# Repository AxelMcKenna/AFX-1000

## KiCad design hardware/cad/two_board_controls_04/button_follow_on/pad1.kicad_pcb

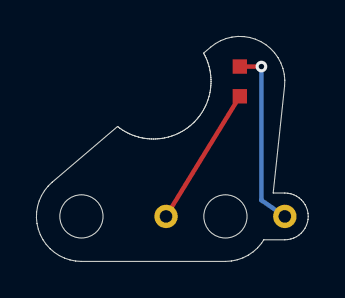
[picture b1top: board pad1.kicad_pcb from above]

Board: 2 copper layers, 15.1 x 12.5 mm, 5 parts (0 on the bottom side), 2 nets.

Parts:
D1: KPT-1608CGCK; KPT1608
H1, H2: Existing holder mount; M2
W1: LED_K; Wire
W2: LED_A; Wire

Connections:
LED_A: D1.2, W2.1
LED_K: D1.1, W1.1

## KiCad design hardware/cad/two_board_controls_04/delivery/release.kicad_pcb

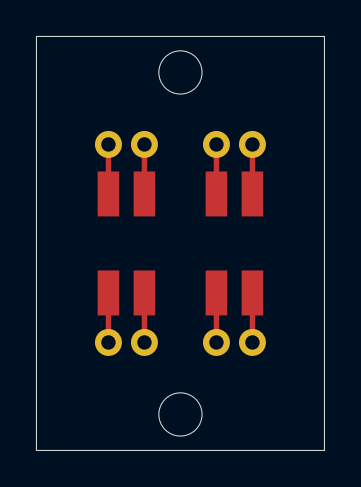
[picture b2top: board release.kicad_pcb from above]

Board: 2 copper layers, 16.0 x 23.0 mm, 11 parts (0 on the bottom side), 8 nets.

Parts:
H1, H2: M2
SW1: JS203011SCQN
W1: SW_PIN_1; WirePad
W2: SW_PIN_2; WirePad
W3: SW_PIN_3; WirePad
W4: SW_PIN_4; WirePad
W5: SW_PIN_5; WirePad
W6: SW_PIN_6; WirePad
W7: SW_PIN_7; WirePad
W8: SW_PIN_8; WirePad

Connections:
SW_PIN_1: SW1.1, W1.1
SW_PIN_2: SW1.2, W2.1
SW_PIN_3: SW1.3, W3.1
SW_PIN_4: SW1.4, W4.1
SW_PIN_5: SW1.5, W5.1
SW_PIN_6: SW1.6, W6.1
SW_PIN_7: SW1.7, W7.1
SW_PIN_8: SW1.8, W8.1

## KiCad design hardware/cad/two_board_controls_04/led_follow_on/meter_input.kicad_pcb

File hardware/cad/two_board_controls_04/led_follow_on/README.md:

# Meter and bank emitter checkpoint

This follow-on implements two 20-emitter meter boards and four copies of one bank-emitter board. The 44 sink channels are bound to the existing integrated signal PCB by `wiring.csv` and its source-hashed review. All emitters are Kingbright KPT-1608CGCK with manufacturer-derived lands, polarity, body tolerances and optical locations. This green population establishes physical fit; final meter color progression and brightness remain optical acceptance work.

Each board is retained with M2 screws, washers and nuts. The printed opaque frame separates meter cells and holds the retained lens flange against the lid. Meter boards occupyZ39.3–40.9; bank boardsZ39.6–41.2. Meter mounts are(43.9,14.75),(100.9,14.75),(43.9,41.75),(100.9,41.75). Bank mounts areX76/95/114/133, each atY97 and 102. Use M2×10 screws with head OD≤4.5, M2 nuts AF4×1.6 and 0.5 mm washers. Meter nuts beginZ37.2, bank nutsZ37.5. Confirm actual hardware and printed stack before assembly.

`meters-r4` passes seven empty clearances (including full button travel and all 42 local wire exits), two retention probes and two printable frames. `banks-r4` passes seven empty clearances, two retention probes and seven printable exports including combined full/split lid and guide. The combined exports include sealed TBH04 display/selector modifications. Existing lenses are retained. `pcb-native-r3/review.json` records zero native DRC violations and zero unconnected items for all three distinct routed board designs. This is board connectivity verification, not schematic ERC or powered qualification.

`banks-r3/led_guide` is retained failed evidence: CGAL emitted two degenerate collinear facets and four bad directed edges. Re-exporting with the pinned Manifold backend passed the same closed-oriented-boundary check in r4; no geometry was weakened to bypass the check. Earlier bank r1 caught incomplete imported button-parameter scope; `button_motion.scad` now imports through the complete housing parameter scope.

For integration use `tbh 05_bank_meter_installed()`, `tbh 05_bank_meter_lid()` and `tbh 05_bank_meter_guide()` from `banks.scad`. The installed module includes purchased-body and local lead reserves for collision review. Frame exports are print-oriented; installed modules use housing datums.

Anode leads need rated harness splices, not several conductors in one crimp. Local wire envelopes reserve only the first 2.5 mm below each board. Full harness routing, strain relief, solder insulation and lid-service loops remain separate gates. Tiny boards and .4 mm cell walls require fabrication/print capability confirmation. There is no physical or optical acceptance claim. Button-indicator and RGB-ring carriers are not implemented by this checkpoint and must not be inferred from the 44 implemented channels.

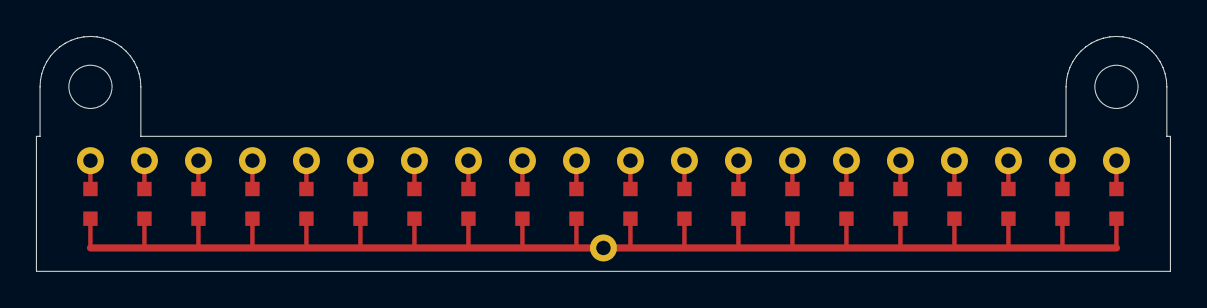
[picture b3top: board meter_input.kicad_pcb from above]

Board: 2 copper layers, 63.0 x 13.1 mm, 43 parts (0 on the bottom side), 21 nets.

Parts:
D1, D2, D3, D4, D5, D6, D7, D8, D9, D10, D11, D12, D13, D14, D15, D16, D17, D18, D19, D20: KPT-1608CGCK; KPT1608
H1, H2: M2
W1: meter_input_0; WirePad
W2: meter_input_1; WirePad
W3: meter_input_2; WirePad
W4: meter_input_3; WirePad
W5: meter_input_4; WirePad
W6: meter_input_5; WirePad
W7: meter_input_6; WirePad
W8: meter_input_7; WirePad
W9: meter_input_8; WirePad
W10: meter_input_9; WirePad
W11: meter_input_10; WirePad
W12: meter_input_11; WirePad
W13: meter_input_12; WirePad
W14: meter_input_13; WirePad
W15: meter_input_14; WirePad
W16: meter_input_15; WirePad
W17: meter_input_16; WirePad
W18: meter_input_17; WirePad
W19: meter_input_18; WirePad
W20: meter_input_19; WirePad
WA: LED_ANODE_5V; WirePad

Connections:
LED_ANODE_5V: D1.2, D2.2, D3.2, D4.2, D5.2, D6.2, D7.2, D8.2, D9.2, D10.2, D11.2, D12.2, D13.2, D14.2, D15.2, D16.2, D17.2, D18.2, D19.2, D20.2, WA.1
meter_input_0: D1.1, W1.1
meter_input_1: D2.1, W2.1
meter_input_2: D3.1, W3.1
meter_input_3: D4.1, W4.1
meter_input_4: D5.1, W5.1
meter_input_5: D6.1, W6.1
meter_input_6: D7.1, W7.1
meter_input_7: D8.1, W8.1
meter_input_8: D9.1, W9.1
meter_input_9: D10.1, W10.1
meter_input_10: D11.1, W11.1
meter_input_11: D12.1, W12.1
meter_input_12: D13.1, W13.1
meter_input_13: D14.1, W14.1
meter_input_14: D15.1, W15.1
meter_input_15: D16.1, W16.1
meter_input_16: D17.1, W17.1
meter_input_17: D18.1, W18.1
meter_input_18: D19.1, W19.1
meter_input_19: D20.1, W20.1
